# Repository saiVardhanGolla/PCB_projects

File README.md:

# PCB_projects
 my PCB design projects

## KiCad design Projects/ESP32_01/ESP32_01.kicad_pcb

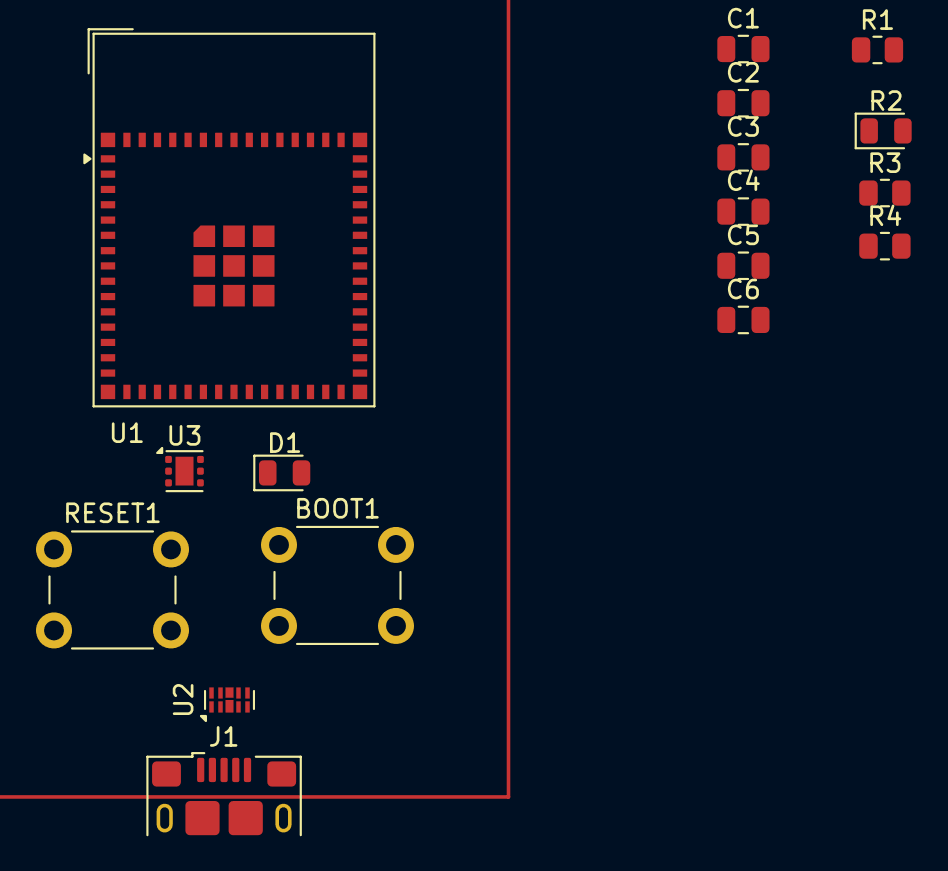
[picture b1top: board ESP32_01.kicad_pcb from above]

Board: 2 copper layers, 17 parts (0 on the bottom side), 11 nets, no tracks yet.

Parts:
BOOT1: SW_PUSH_6mm
C1, C2, C3, C4: 0.1uF; C_0805_2012Metric
C5, C6: 10uF; C_0805_2012Metric
D1: LED; LED_0805_2012Metric
J1: USB_B_Micro; USB_Micro-B_Amphenol_10118193-0002LF_Horizontal
R1: 10k; R_0805_2012Metric
R2: 1M; LED_0805_2012Metric
R3: 200k; R_0805_2012Metric
R4: 5.1k; R_0805_2012Metric
RESET1: SW_PUSH_6mm
U1: ESP32-S3-MINI-1; ESP32-S2-MINI-1
U2: D3V3XA4B10LP; Diodes_UDFN-10_1.0x2.5mm_P0.5mm
U3: TLV75801PDRV; WSON-6-1EP_2x2mm_P0.65mm_EP1x1.6mm

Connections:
GND: BOOT1.1, C1.2, C2.2, C3.2, C4.2, C5.2, C6.2, D1.1 (K), J1.5 (GND), J1.6 (Shield), R3.2, RESET1.1, U1.1 (GND), U1.2 (GND), U1.42 (GND), U1.43 (GND), U1.46 (GND), U1.47 (GND), U1.48 (GND), U1.49 (GND), U1.50 (GND), U1.51 (GND), U1.52 (GND), U1.53 (GND), U1.54 (GND), U1.55 (GND), U1.56 (GND), U1.57 (GND), U1.58 (GND), U1.59 (GND), U1.60 (GND), U1.61 (GND), U1.62 (GND), U1.63 (GND), U1.64 (GND), U1.65 (GND), U2.3 (VSS), U2.8 (VSS), U3.3 (GND), U3.7 (GND)
unnamed: D1.2 (A), R4.2
unnamed: J1.3 (D+), U2.2, U2.9 (NC)
unnamed: J1.2 (D-), U2.1, U2.10 (NC)
unnamed: J1.1 (VBUS), U2.4, U2.7 (NC)
unnamed: C1.1, C2.1, U1.3 (3V3)
unnamed: C3.1, R1.2, RESET1.2, U1.45 (EN)
unnamed: BOOT1.2, C4.1, U1.4 (IO0)
unnamed: C6.1, U3.4 (EN), U3.6 (IN)
unnamed: R2.2, R3.1, U3.2 (FB)
unnamed: C5.1, R2.1, R4.1, U3.1 (OUT)

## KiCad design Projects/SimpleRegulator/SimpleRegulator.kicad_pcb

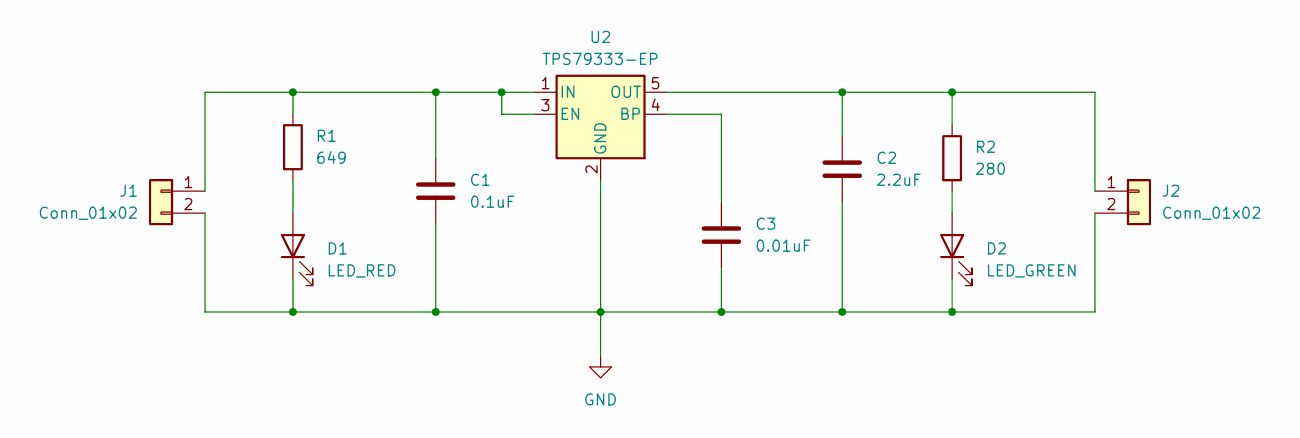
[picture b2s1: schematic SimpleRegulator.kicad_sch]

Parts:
C1: 0.1uF; C_0805_2012Metric
C2: 2.2uF; C_0805_2012Metric
C3: 0.01uF; C_0805_2012Metric
D1: LED_RED; LED_0805_2012Metric
D2: LED_GREEN; LED_0805_2012Metric
J1, J2: Conn_01x02; PinHeader_1x02_P2.54mm_Horizontal
R1: 649; R_0805_2012Metric
R2: 280; R_0805_2012Metric
U2: TPS79333-EP; SOT-23-5

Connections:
GND: C1.2, C2.2, C3.2, D1.1 (K), D2.1 (K), J1.2, J2.2, U2.2 (GND)
unnamed: D1.2 (A), R1.2
unnamed: D2.2 (A), R2.2
unnamed: C1.1, J1.1, R1.1, U2.1 (IN), U2.3 (EN)
unnamed: C2.1, J2.1, R2.1, U2.5 (OUT)
unnamed: C3.1, U2.4 (BP)

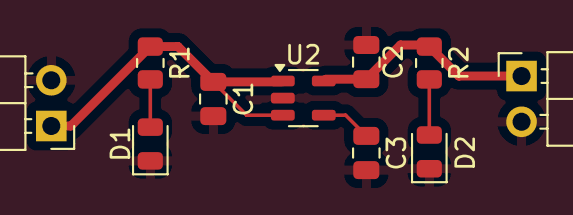
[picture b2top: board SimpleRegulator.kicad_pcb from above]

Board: 2 copper layers, 10 parts (0 on the bottom side), 6 nets.

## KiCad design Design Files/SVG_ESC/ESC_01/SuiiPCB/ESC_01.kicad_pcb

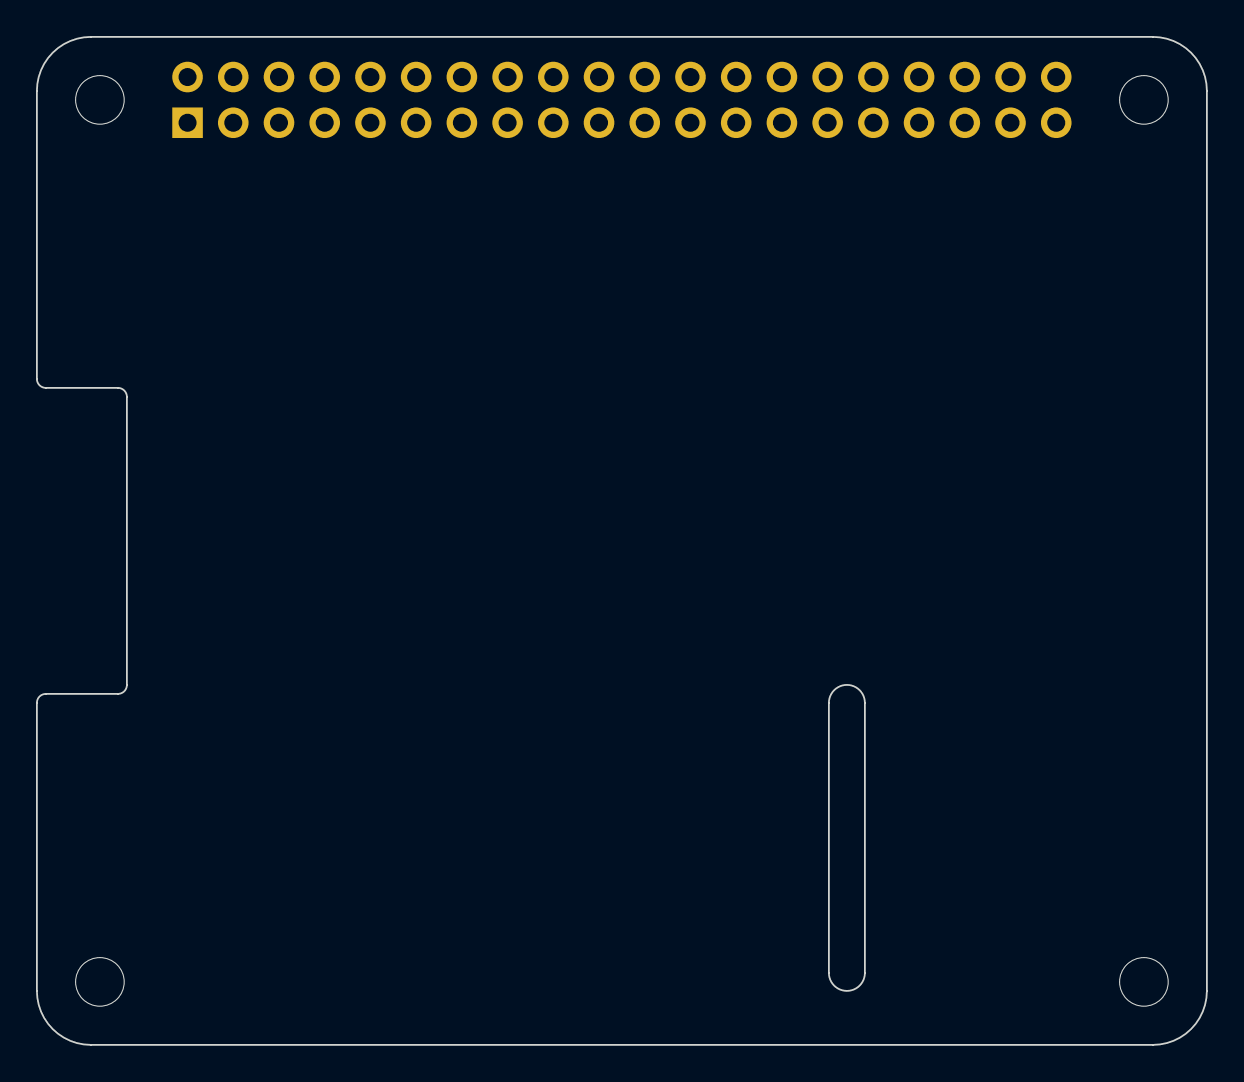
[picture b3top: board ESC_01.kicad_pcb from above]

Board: 2 copper layers, 65.0 x 56.0 mm, 5 parts (1 on the bottom side), 3 nets, no tracks yet.

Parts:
J1: GPIO; PinSocket_2x20_P2.54mm_Vertical
MH1, MH2, MH3, MH4: MountingHole_2.7mm_M2.5

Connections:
+3V3: J1.1, J1.17
+5V: J1.2, J1.4
GND: J1.6, J1.9, J1.14, J1.20, J1.25, J1.30, J1.34, J1.39

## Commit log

2025-01-25 0.01
2025-01-27 P2_0.0
